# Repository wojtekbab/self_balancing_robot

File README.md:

# Two-Wheeled Balancing Robot Project

## Overview
Repository contains code for microcontroller ESP-32 with implemented control system with LQR regulator. Microcontroller connects to local network and acts like a web server, providing GUI on website to control vehicle. Matlab scripts were used to calculate mathematical model and simulink system was designed to veryficate close loop system. 

## Table of Contents
1. [ESP32 Code](#esp32-code)
2. [MATLAB Code](#matlab-code)
3. [Inventor Project](#inventor-project)
4. [KiCad Project](#kicad-project)

## ESP32 Code
Code was written in PlatformIO extension with arduino framework. FreeRTOS was used with hardware interrupts and tasks for:
- service encoders
- measure imu data
- filter data with Kalman Filter
- calculate rest of state variables
- generate reference vector
- calculate control for motors
- log data 

### Files
- `main.cpp`: main file for the ESP32.
- `defines.cpp`: file with defines.
- `globals.cpp`: file with global variables used by tasks.
- `interrupts.cpp`: interrupts service routines.
- `utilities.cpp`: some utility functions.
- `tasks.cpp`: file with FreeRTOS tasks.
- `web_server.cpp`: web server with html page.
- `platformio.ini`: configuration file used by PlatformIO extension.

### How to Run
1. Create empty project with PlatformIO.
2. Copy `platformio.ini` file into project.
3. Copy header and source files into folder src.

## MATLAB Code
The MATLAB code is used to calculate mathematical model and simulate system.

### Files
- `s1_parameters.m`: script with system parameters.
- `s2_mathematical_model.m`: script for calculate unlinear and linear model as state-space matrixes.
- `sim1_unlinear_model_with_LQR.slx`: simulink close loop system with LQR regulator 

### How to Run
1. Open Matlab 2023b.
2. Run `s2_mathematical_model.m` to load parameters and calculate K matrix.
3. Run `sim1_unlinear_model_with_LQR.slx` to test system output for given reference velocities or different initial state.

## Python Code
In case when Matlab is not available, all necessary scripts were translated for python.

### Files
- `requirements.txt`: contain all necessary python modules.
- `parameters.py`: contain dictionary with system parameters.
- `p1_mathematical_model.ipynb`: notebook for symbolic equations with sympy to obtain mathematical model.
- `p2_closed_loop_system.ipynb`: notebook to make simulations with closed loop system with LQR regulator  

### How to Run
1. Install necessary modules.
2. Run `p1_mathematical_model.ipynb` to obtain mathematical model.
3. Run `p2_closed_loop_system.ipynb` to see result of system simulations.

## Inventor Project
Image from Inventor project was included to repository. 3D model was created to design distribution of elements and to calculate parameters of vehicle inertia. 

### Images
<div align="left">

    <p><em>Figure 1: 3D model from Autodesk Inventor and real model.</em></p>
</div>

## KiCad Project
Images from KiCad project was included to repository. PCB board was created for electronic parts from system to avoid EMI interferences from DC motors.

### Images
<div align="left">

    <p><em>Figure 2: designed paths, visualization, home made board</em></p>
</div>

## Demo

<p>
  Link to demo video:
  <a href="https://www.youtube.com/watch?v=7iqSqyg-NeA" >https://www.youtube.com/watch?v=7iqSqyg-NeA</a>
</p>

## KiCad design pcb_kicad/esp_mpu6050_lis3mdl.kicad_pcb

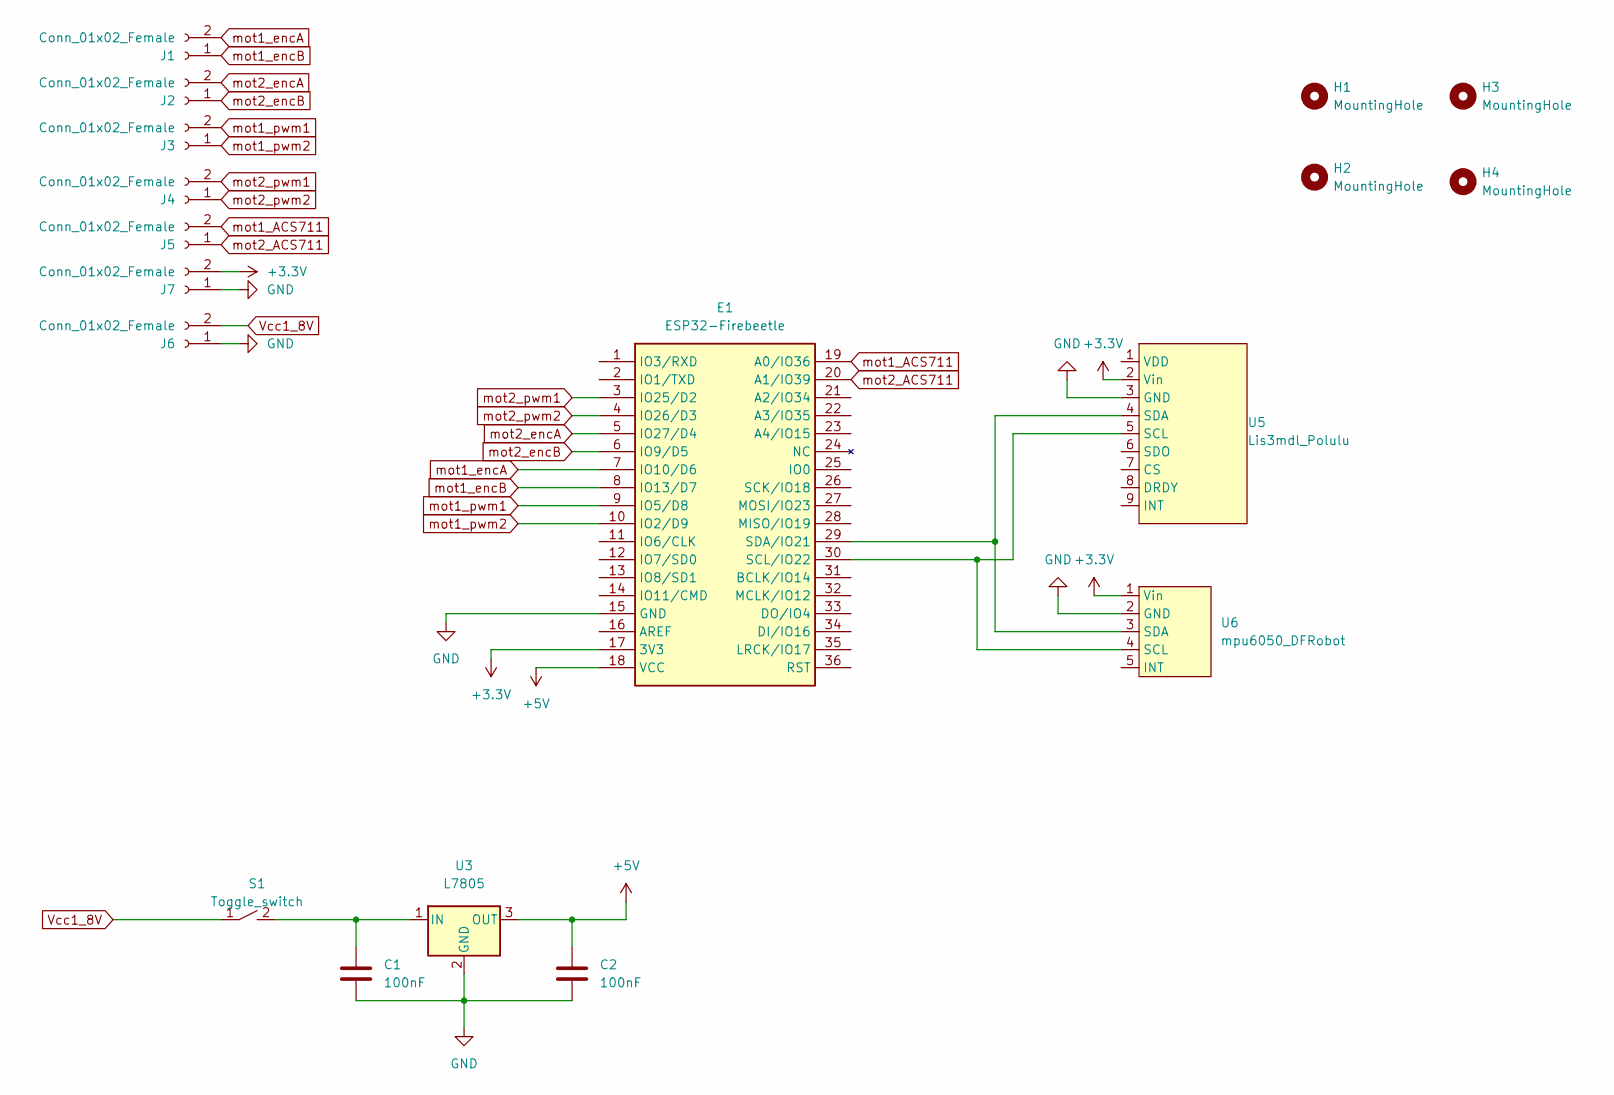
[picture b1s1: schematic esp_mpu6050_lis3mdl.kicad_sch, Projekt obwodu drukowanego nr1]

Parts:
C1, C2: 100nF; C_Disc_D5.0mm_W2.5mm_P2.50mm
E1: ESP32-Firebeetle; FIREBEETLE_ESP32
H1, H2, H3, H4: MountingHole; MountingHole_3.2mm_M3_DIN965_Pad
J1, J2, J3, J4, J5, J6, J7: Conn_01x02_Female; zlacze ARK_2
S1: Toggle_switch; mini_black_switch
U3: L7805; LM78xx
U5: Lis3mdl_Polulu; lis3mdl_Pololu
U6: mpu6050_DFRobot

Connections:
+3.3V: E1.17 (3V3), J7.2, U5.2 (Vin), U6.1 (Vin)
+5V: C2.1, E1.18 (VCC), U3.3 (OUT)
GND: C1.2, C2.2, E1.15 (GND), J6.1, J7.1, U3.2 (GND), U5.3 (GND), U6.2 (GND)
unnamed: C1.1, S1.2, U3.1 (IN)
unnamed: E1.29 (SDA/IO21), U5.4 (SDA), U6.3 (SDA)
unnamed: E1.30 (SCL/IO22), U5.5 (SCL), U6.4 (SCL)
Vcc1_8V: J6.2, S1.1
mot1_ACS711: E1.19 (A0/IO36), J5.2
mot1_encA: E1.7 (IO10/D6), J1.2
mot1_encB: E1.8 (IO13/D7), J1.1
mot1_pwm1: E1.9 (IO5/D8), J3.2
mot1_pwm2: E1.10 (IO2/D9), J3.1
mot2_ACS711: E1.20 (A1/IO39), J5.1
mot2_encA: E1.5 (IO27/D4), J2.2
mot2_encB: E1.6 (IO9/D5), J2.1
mot2_pwm1: E1.3 (IO25/D2), J4.2
mot2_pwm2: E1.4 (IO26/D3), J4.1

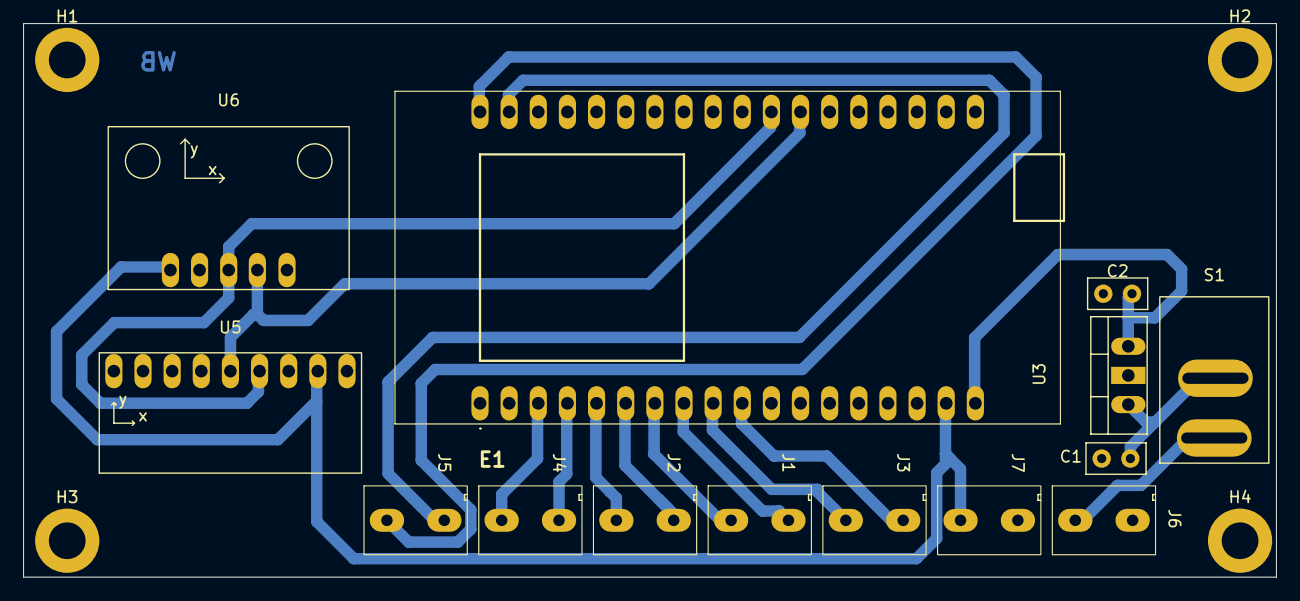
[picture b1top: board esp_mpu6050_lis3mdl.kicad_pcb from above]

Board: 2 copper layers, 109.2 x 48.3 mm, 18 parts (0 on the bottom side), 17 nets.

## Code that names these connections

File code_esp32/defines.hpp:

/**
 * @file defines.hpp
 * @author Wojciech Babicki (wojciech.babicki@op.pl)
 * @brief 
 * @version 0.1
 * @date 2024-07-15
 * 
 * @copyright Copyright (c) 2024
 * 
 */
#ifndef DEFINES_HPP
#define DEFINES_HPP

#include <freertos/FreeRTOS.h> 

// encoder pins
#define GPIO_MOT1_ENCA 10
#define GPIO_MOT1_ENCB 13
#define GPIO_MOT2_ENCA 27
#define GPIO_MOT2_ENCB 9

// pwm pins for control motors
#define GPIO_MOT1_PWM_R 5
#define GPIO_MOT1_PWM_L 2
#define GPIO_MOT2_PWM_R 25
#define GPIO_MOT2_PWM_L 26

// max references for html page control
#define REFERENCE_X_DOT_MAX 0.5f
#define REFERENCE_PSI_DOT_MAX 1.57f

// queue length (used for data from html page) 
#define QUEUE_JOYSTICK_LENGTH 1

// use core 1 for user program
#if CONFIG_FREERTOS_UNICORE
static const BaseType_t app_cpu = 0;
#else
static const BaseType_t app_cpu = 1;
#endif

// for group event
#define START_STOP_BIT (1 << 0)

#endif // DEFINES_HPP

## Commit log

2024-07-15 add files
2024-07-16 changes in readme
2024-07-16 added event group for button
2024-07-16 edit readme
2024-07-20 add utilities.cpp description
2024-09-02 add python alternative for matlab
